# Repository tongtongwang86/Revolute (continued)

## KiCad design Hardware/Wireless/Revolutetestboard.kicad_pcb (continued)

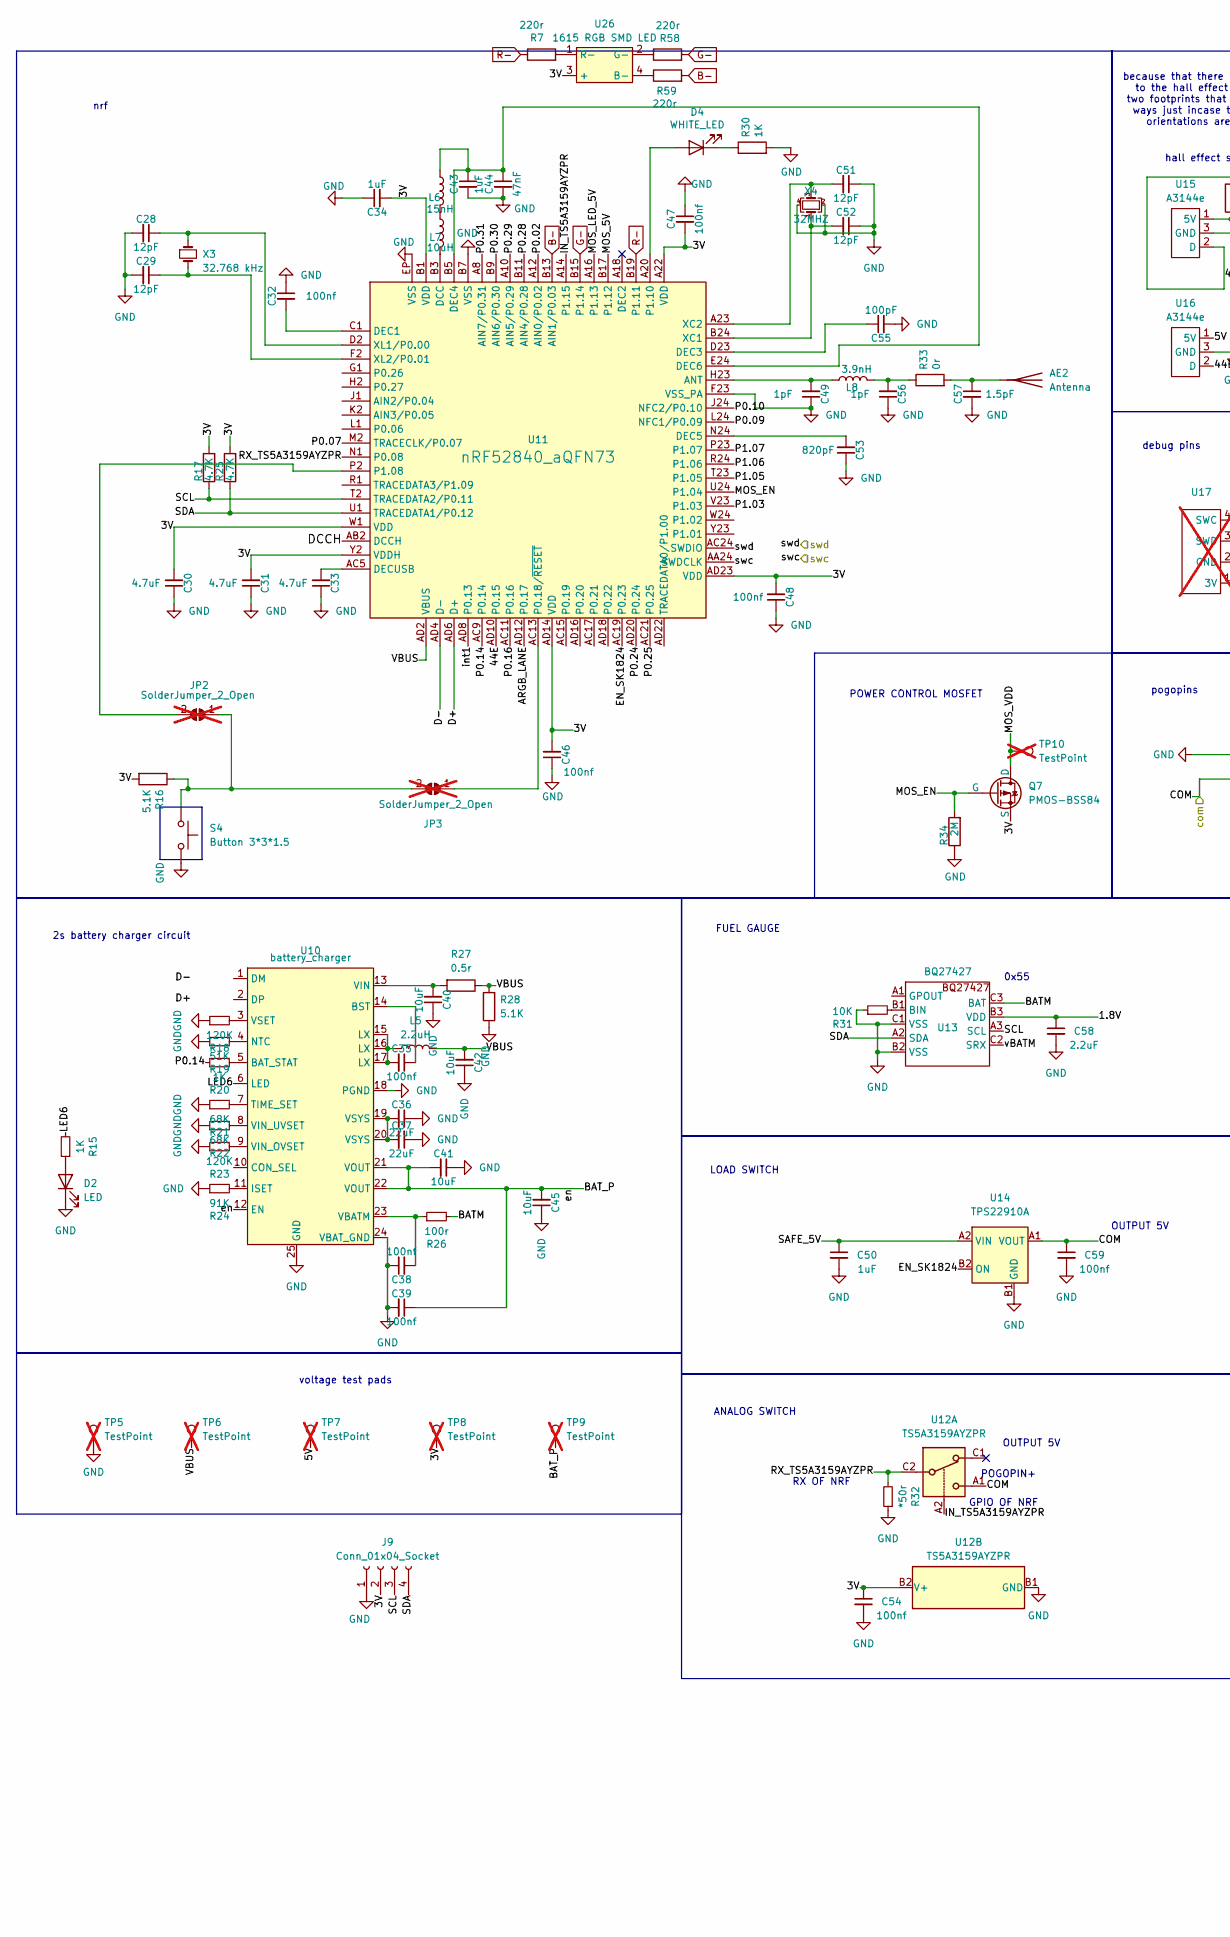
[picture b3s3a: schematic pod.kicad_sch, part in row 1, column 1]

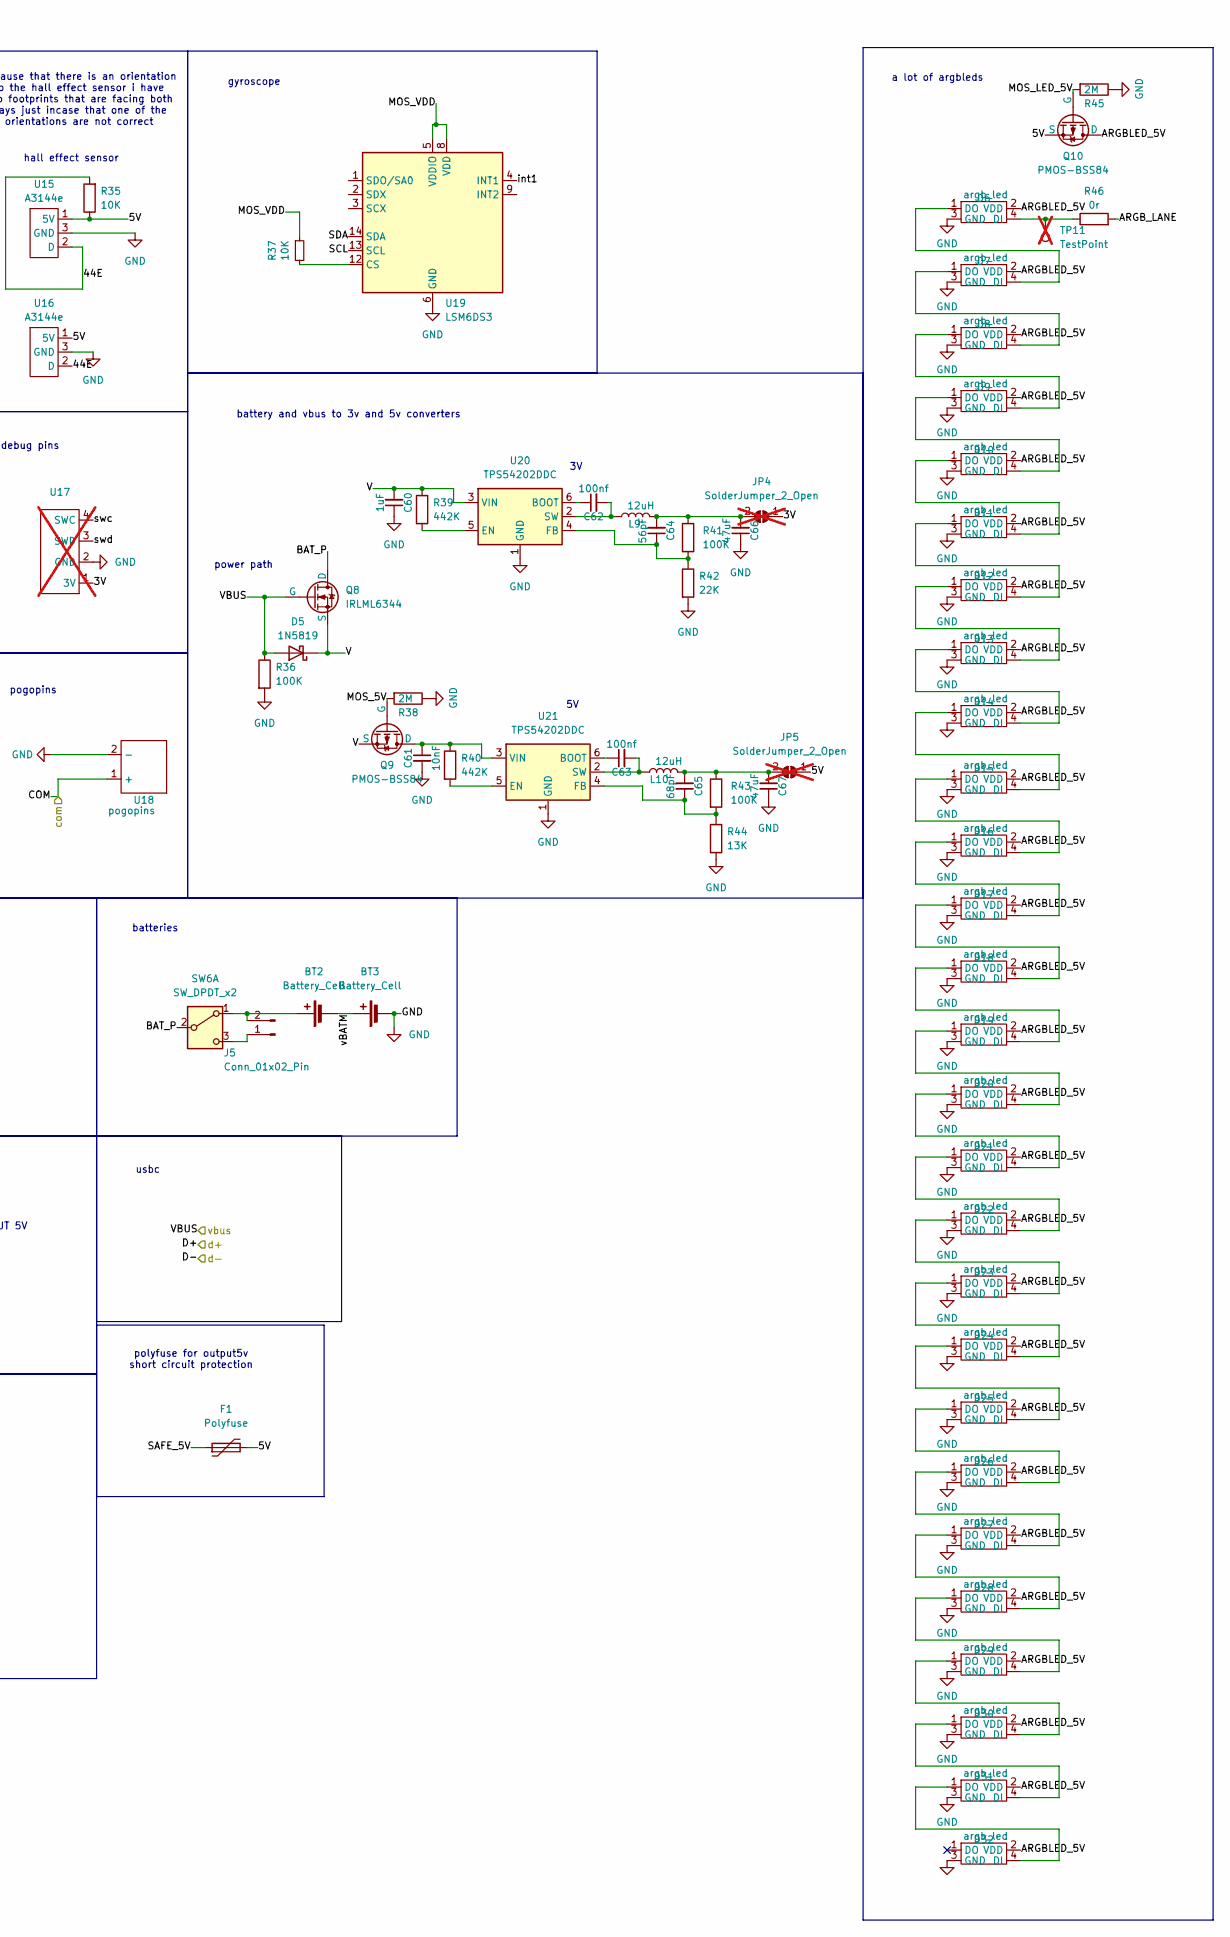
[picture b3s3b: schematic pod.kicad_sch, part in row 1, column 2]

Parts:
AE2: Antenna; 2.4GHz-meander-antenna
BT2, BT3: Battery_Cell; BatteryHolder_Keystone_1057_1x2032
C28, C29, C51, C52: 12pF; 0402
C30, C31, C33: 4.7uF; 0402
C32, C35, C38, C39, C46, C47, C48, C54, C59, C62, C63: 100nf; 0402
C34, C43, C50, C60: 1uF; 0402
C36, C37: 22uF; 0402
C40, C41, C42, C45: 10uF; 0402
C44: 47nF; 0402
C49, C56: 1pF; 0402
C53: 820pF; 0402
C55: 100pF; 0402
C57: 1.5pF; 0402
C58: 2.2uF; 0402
C61: 10nF; 0402
C64: 56pF; 0402
C65: 68pF; 0402
C66, C67: 47uF; 0402
D2: LED; LED_0402_1005Metric
D4: WHITE_LED; LED_0402_1005Metric
D5: 1N5819; D_SOD-323_HandSoldering
D6, D7, D8, D9, D10, D11, D12, D13, D14, D15, D16, D17, D18, D19, D20, D21, D22, D23, D24, D25, D26, D27, D28, D29, D30, D31, D32: argb_led; Led-ARGB
F1: Polyfuse; R_0805_2012Metric
J5: Conn_01x02_Pin; PinHeader_1x02_P2.54mm_Vertical
J9: Conn_01x04_Socket; PinSocket_1x04_P2.54mm_Vertical
JP2, JP3, JP4, JP5: SolderJumper_2_Open; SolderBridge; not fitted
L5: 2.2uH; L_Chilisin_BMRA00050520
L6: 15nH; 0402
L7: 10uH; 0402
L8: 3.9nH; L_0402_1005Metric
L9, L10: 12uH; L_0603_1608Metric
Q7, Q9, Q10: PMOS-BSS84; SOT-23-3
Q8: IRLML6344; TSOT-23
R7, R58, R59: 220r; R_0402_1005Metric
R15, R20, R30: 1K; R_0402_1005Metric
R16, R28: 5.1K; R_0402_1005Metric
R17, R25: 4.7K; 0402
R18, R23: 120K; R_0402_1005Metric
R19: 51K; R_0402_1005Metric
R21, R22: 68K; R_0402_1005Metric
R24: 91K; R_0402_1005Metric
R26: 100r; R_0402_1005Metric
R27: 0.5r; R_0402_1005Metric
R31: 10K; 0402
R32: *50r; R_0402_1005Metric
R33, R46: 0r; 0402
R34, R38, R45: 2M; 0402
R35, R37: 10K; R_0402_1005Metric
R36, R41, R43: 100K; R_0402_1005Metric
R39, R40: 442K; R_0402_1005Metric
R42: 22K; R_0402_1005Metric
R44: 13K; R_0402_1005Metric
S4: Button 3*3*1.5; button 3x3
SW6: SW_DPDT_x2; MST-12C05 SLIDEBUTTON
TP5, TP6, TP7, TP8, TP9, TP10, TP11: TestPoint; TestPoint_Pad_D1.0mm; not fitted
U10: battery_charger; QFN-24-1EP_4x4mm_P0.5mm_EP2.7x2.6mm
U11: nRF52840_aQFN73; AQFN-73-1EP_7x7mm_P0.5mm_NRF52840-custom
U12: TS5A3159AYZPR; Texas_DSBGA-6_0.9x1.4mm_Layout2x3_P0.5mm
U13: BQ27427; Texas_DSBGA-9_1.62mmx1.58mm_Layout3x3_P0.5mm
U14: TPS22910A; BGA4N50P2X2_88X88X50N
U15, U16: A3144e; TSOT-23
U17: debug pins; not fitted
U18: pogopins; pogopin
U19: LSM6DS3; LGA-14_3x2.5mm_P0.5mm_LayoutBorder3x4y
U20, U21: TPS54202DDC; SOT-23-6
U26: 1615 RGB SMD LED
X3: 32.768 kHz; Crystal_SMD_2012-2Pin_2.0x1.2mm; Manufacturer Part SC20S-12.5PF20PPM; LCSC Part C97607
X4: 32MHZ; Crystal_SMD_2016-4Pin_2.0x1.6mm

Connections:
/pod/1.8V: C58.1, U13.B3 (VDD)
/pod/3V: C30.2, C31.2, C34.2, C46.2, C47.2, C48.2, C54.1, J9.2, JP4.1 (A), Q7.2 (S), R16.2, R17.2, R25.2, TP8.1, U11.A22 (VDD), U11.AD14 (VDD), U11.AD23 (VDD), U11.B1 (VDD), U11.W1 (VDD), U11.Y2 (VDDH), U12.B2 (V+), U17.1 (3V), U26.3 (+)
/pod/5V: F1.2, JP5.1 (A), Q10.2 (S), R35.1, TP7.1, U15.1 (5V), U16.1 (5V)
/pod/44E: R35.2, U11.AD10 (P0.15), U15.2 (D), U16.2 (D)
/pod/ARGBLED_5V: D6.2 (VDD), D7.2 (VDD), D8.2 (VDD), D9.2 (VDD), D10.2 (VDD), D11.2 (VDD), D12.2 (VDD), D13.2 (VDD), D14.2 (VDD), D15.2 (VDD), D16.2 (VDD), D17.2 (VDD), D18.2 (VDD), D19.2 (VDD), D20.2 (VDD), D21.2 (VDD), D22.2 (VDD), D23.2 (VDD), D24.2 (VDD), D25.2 (VDD), D26.2 (VDD), D27.2 (VDD), D28.2 (VDD), D29.2 (VDD), D30.2 (VDD), D31.2 (VDD), D32.2 (VDD), Q10.3 (D)
/pod/ARGB_LANE: R46.2, U11.AD12 (P0.17)
/pod/BATM: R26.2, U13.C3 (BAT)
/pod/BAT_P: C39.1, C41.2, C45.2, Q8.3 (D), SW6.2 (B), TP9.1, U10.12 (EN), U10.21 (VOUT), U10.22 (VOUT)
/pod/COM: C59.1, U12.A1, U14.A1 (VOUT), U18.1 (+); also elsewhere on the board
/pod/D+: U11.AD6 (D+); also elsewhere on the board
/pod/D-: U11.AD4 (D-); also elsewhere on the board
/pod/DCCH: U11.AB2 (DCCH)
/pod/EN_SK1824: U11.AC19 (P0.23), U14.B2 (ON)
/pod/IN_TS5A3159AYZPR: U11.A14 (P1.15), U12.A2
/pod/LED6: R15.2, U10.6 (LED)
/pod/MOS_5V: Q9.1 (G), R38.2, U11.B17 (P1.12)
/pod/MOS_EN: Q7.1 (G), R34.2, U11.U24 (P1.04)
/pod/MOS_LED_5V: Q10.1 (G), R45.2, U11.A16 (P1.13)
/pod/MOS_VDD: Q7.3 (D), R37.1, TP10.1, U19.5 (VDDIO), U19.8 (VDD)
/pod/P0.02: U11.A12 (AIN0/P0.02)
/pod/P0.07: U11.M2 (TRACECLK/P0.07)
/pod/P0.09: U11.L24 (NFC1/P0.09)
/pod/P0.10: U11.J24 (NFC2/P0.10)
/pod/P0.14: R20.1, U11.AC9 (P0.14)
/pod/P0.16: U11.AC11 (P0.16)
/pod/P0.24: U11.AD20 (P0.24)
/pod/P0.25: U11.AC21 (P0.25)
/pod/P0.28: U11.B11 (AIN4/P0.28)
/pod/P0.29: U11.A10 (AIN5/P0.29)
/pod/P0.30: U11.B9 (AIN6/P0.30)
/pod/P0.31: U11.A8 (AIN7/P0.31)
/pod/P1.03: U11.V23 (P1.03)
/pod/P1.05: U11.T23 (P1.05)
/pod/P1.06: U11.R24 (P1.06)
/pod/P1.07: U11.P23 (P1.07)
/pod/RX_TS5A3159AYZPR: R32.2, U11.N1 (P0.08), U12.C2
/pod/SAFE_5V: C50.1, F1.1, U14.A2 (VIN)
/pod/SCL: J9.3, R17.1, U11.T2 (TRACEDATA2/P0.11), U13.A3 (SCL), U19.13 (SCL)
/pod/SDA: J9.4, R25.1, U11.U1 (TRACEDATA1/P0.12), U13.A2 (SDA), U19.14 (SDA)
/pod/V: C60.2, D5.1 (K), Q8.2 (S), Q9.2 (S), R39.1, U20.3 (VIN)
/pod/VBUS: C42.2, D5.2 (A), L5.2, Q8.1 (G), R27.1, R28.2, R36.1, TP6.1, U11.AD2 (VBUS); also elsewhere on the board
/pod/int1: U11.AD8 (P0.13), U19.4 (INT1)
/pod/swc: U11.AA24 (SWDCLK), U17.4 (SWC); also elsewhere on the board
/pod/swd: U11.AC24 (SWDIO), U17.3 (SWD); also elsewhere on the board
/pod/vBATM: BT2.2 (-), BT3.1 (+), U13.C2 (SRX)
B-: R59.2, U11.B13 (AIN1/P0.03)
G-: R58.2, U11.B15 (P1.14)
GND: BT3.2 (-), C28.2, C29.2, C30.1, C31.1, C32.1, C33.1, C34.1, C36.1, C37.1, C38.1, C39.2, C40.1, C41.1, C42.1, C43.2, C44.2, C45.1, C46.1, C47.1, C48.1, C49.1, C50.2, C51.1, C52.1, C53.1, C54.2, C55.2, C56.1, C57.2, C58.2, C59.2, C60.1, C61.2, C66.1, C67.1, D2.1 (K), D6.3 (GND), D7.3 (GND), D8.3 (GND), D9.3 (GND), D10.3 (GND), D11.3 (GND), D12.3 (GND), D13.3 (GND), D14.3 (GND), D15.3 (GND), D16.3 (GND), D17.3 (GND), D18.3 (GND), D19.3 (GND), D20.3 (GND), D21.3 (GND), D22.3 (GND), D23.3 (GND), D24.3 (GND), D25.3 (GND), D26.3 (GND), D27.3 (GND), D28.3 (GND), D29.3 (GND), D30.3 (GND), D31.3 (GND), D32.3 (GND), J9.1, R18.1, R19.1, R21.1, R22.1, R23.1, R24.1, R28.1, R30.2, R31.1, R32.1, R34.1, R36.2, R38.1, R42.2, R44.2, R45.1, S4.2, TP5.1, U10.18 (PGND), U10.24 (VBAT_GND), U10.25 (GND), U11.B7 (VSS), U11.EP (VSS), U11.F23 (VSS_PA), U12.B1 (GND), U13.B2 (VSS), U13.C1 (VSS), U14.B1 (GND), U15.3 (GND), U16.3 (GND), U17.2 (GND), U18.2 (-), U19.6 (GND), U19.7 (GND), U20.1 (GND), U21.1 (GND), X4.2, X4.4; also elsewhere on the board
unnamed: AE2.1 (A), C57.1, R33.2
unnamed: BT2.1 (+), J5.2, SW6.1 (A)
unnamed: C35.2, L5.1, U10.15 (LX), U10.16 (LX), U10.17 (LX)
unnamed: C36.2, C37.2, U10.19 (VSYS), U10.20 (VSYS)
unnamed: C56.2, L8.2, R33.1
unnamed: D2.2 (A), R15.1
unnamed: D4.2 (A), U11.A20 (P1.10)
unnamed: D4.1 (K), R30.1
unnamed: D6.4 (DI), R46.1, TP11.1
unnamed: D6.1 (DO), D7.4 (DI)
unnamed: D7.1 (DO), D8.4 (DI)
unnamed: D8.1 (DO), D9.4 (DI)
unnamed: D9.1 (DO), D10.4 (DI)
unnamed: D10.1 (DO), D11.4 (DI)
unnamed: D11.1 (DO), D12.4 (DI)
unnamed: D12.1 (DO), D13.4 (DI)
unnamed: D13.1 (DO), D14.4 (DI)
unnamed: D14.1 (DO), D15.4 (DI)
unnamed: D15.1 (DO), D16.4 (DI)
unnamed: D16.1 (DO), D17.4 (DI)
unnamed: D17.1 (DO), D18.4 (DI)
unnamed: D18.1 (DO), D19.4 (DI)
unnamed: D19.1 (DO), D20.4 (DI)
unnamed: D20.1 (DO), D21.4 (DI)
unnamed: D21.1 (DO), D22.4 (DI)
unnamed: D22.1 (DO), D23.4 (DI)
unnamed: D23.1 (DO), D24.4 (DI)
unnamed: D24.1 (DO), D25.4 (DI)
unnamed: D25.1 (DO), D26.4 (DI)
unnamed: D26.1 (DO), D27.4 (DI)
unnamed: D27.1 (DO), D28.4 (DI)
unnamed: D28.1 (DO), D29.4 (DI)
unnamed: D29.1 (DO), D30.4 (DI)
unnamed: D30.1 (DO), D31.4 (DI)
unnamed: D31.1 (DO), D32.4 (DI)
unnamed: J5.1, SW6.3 (C)
unnamed: JP2.1 (A), JP3.2 (B), R16.1, S4.1
unnamed: JP2.2 (B), U11.P2 (P1.08)
unnamed: JP3.1 (A), U11.AC13 (P0.18/~RESET)
unnamed: C64.2, C66.2, JP4.2 (B), L9.2, R41.1
unnamed: C65.2, C67.2, JP5.2 (B), L10.2, R43.1
unnamed: L6.2, L7.1
unnamed: C61.1, Q9.3 (D), R40.1, U21.3 (VIN)
unnamed: R20.2, U10.5 (BAT_STAT)
unnamed: C35.1, U10.14 (BST)
unnamed: R24.2, U10.11 (ISET)
unnamed: R19.2, U10.4 (NTC)
unnamed: R21.2, U10.7 (TIME_SET)
unnamed: C38.2, R26.1, U10.23 (VBATM)
unnamed: C40.2, R27.2, U10.13 (VIN)
unnamed: R23.2, U10.9 (VIN_OVSET)
unnamed: R22.2, U10.8 (VIN_UVSET)
unnamed: R18.2, U10.3 (VSET)
unnamed: C49.2, L8.1, U11.H23 (ANT)
unnamed: L7.2, U11.B3 (DCC)
unnamed: C32.2, U11.C1 (DEC1)
unnamed: C55.1, U11.D23 (DEC3)
unnamed: C43.1, C44.1, L6.1, U11.B5 (DEC4), U11.E24 (DEC6)
unnamed: C53.2, U11.N24 (DEC5)
unnamed: C33.2, U11.AC5 (DECUSB)
unnamed: C52.2, U11.B24 (XC1), X4.1
unnamed: C51.2, U11.A23 (XC2), X4.3
unnamed: C28.1, U11.D2 (XL1/P0.00), X3.1
unnamed: C29.1, U11.F2 (XL2/P0.01), X3.2
unnamed: R31.2, U13.B1 (BIN)
unnamed: R37.2, U19.12 (CS)
unnamed: C62.1, U20.6 (BOOT)
unnamed: R39.2, U20.5 (EN)
unnamed: C64.1, R41.2, R42.1, U20.4 (FB)
unnamed: C62.2, L9.1, U20.2 (SW)
unnamed: C63.1, U21.6 (BOOT)
unnamed: R40.2, U21.5 (EN)
unnamed: C65.1, R43.2, R44.1, U21.4 (FB)
unnamed: C63.2, L10.1, U21.2 (SW)
unnamed: R59.1, U26.4 (B-)
unnamed: R58.1, U26.2 (G-)
unnamed: R7.2, U26.1 (R-)
R-: R7.1, U11.B19 (P1.11)

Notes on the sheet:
a lot of argbleds
2s battery charger circuit
usbc
RX OF NRF
0x55
ANALOG SWITCH
POGOPIN+
polyfuse for output5v short circuit protection
OUTPUT 5V
power path
debug pins
battery and vbus to 3v and 5v converters
POWER CONTROL MOSFET
gyroscope
FUEL GAUGE
batteries
because that there is an orientation to the hall effect sensor i have two footprints that are facing both ways just incase that one of the orientations are not correct
voltage test pads
pogopins
nrf
hall effect sensor
LOAD SWITCH
GPIO OF NRF

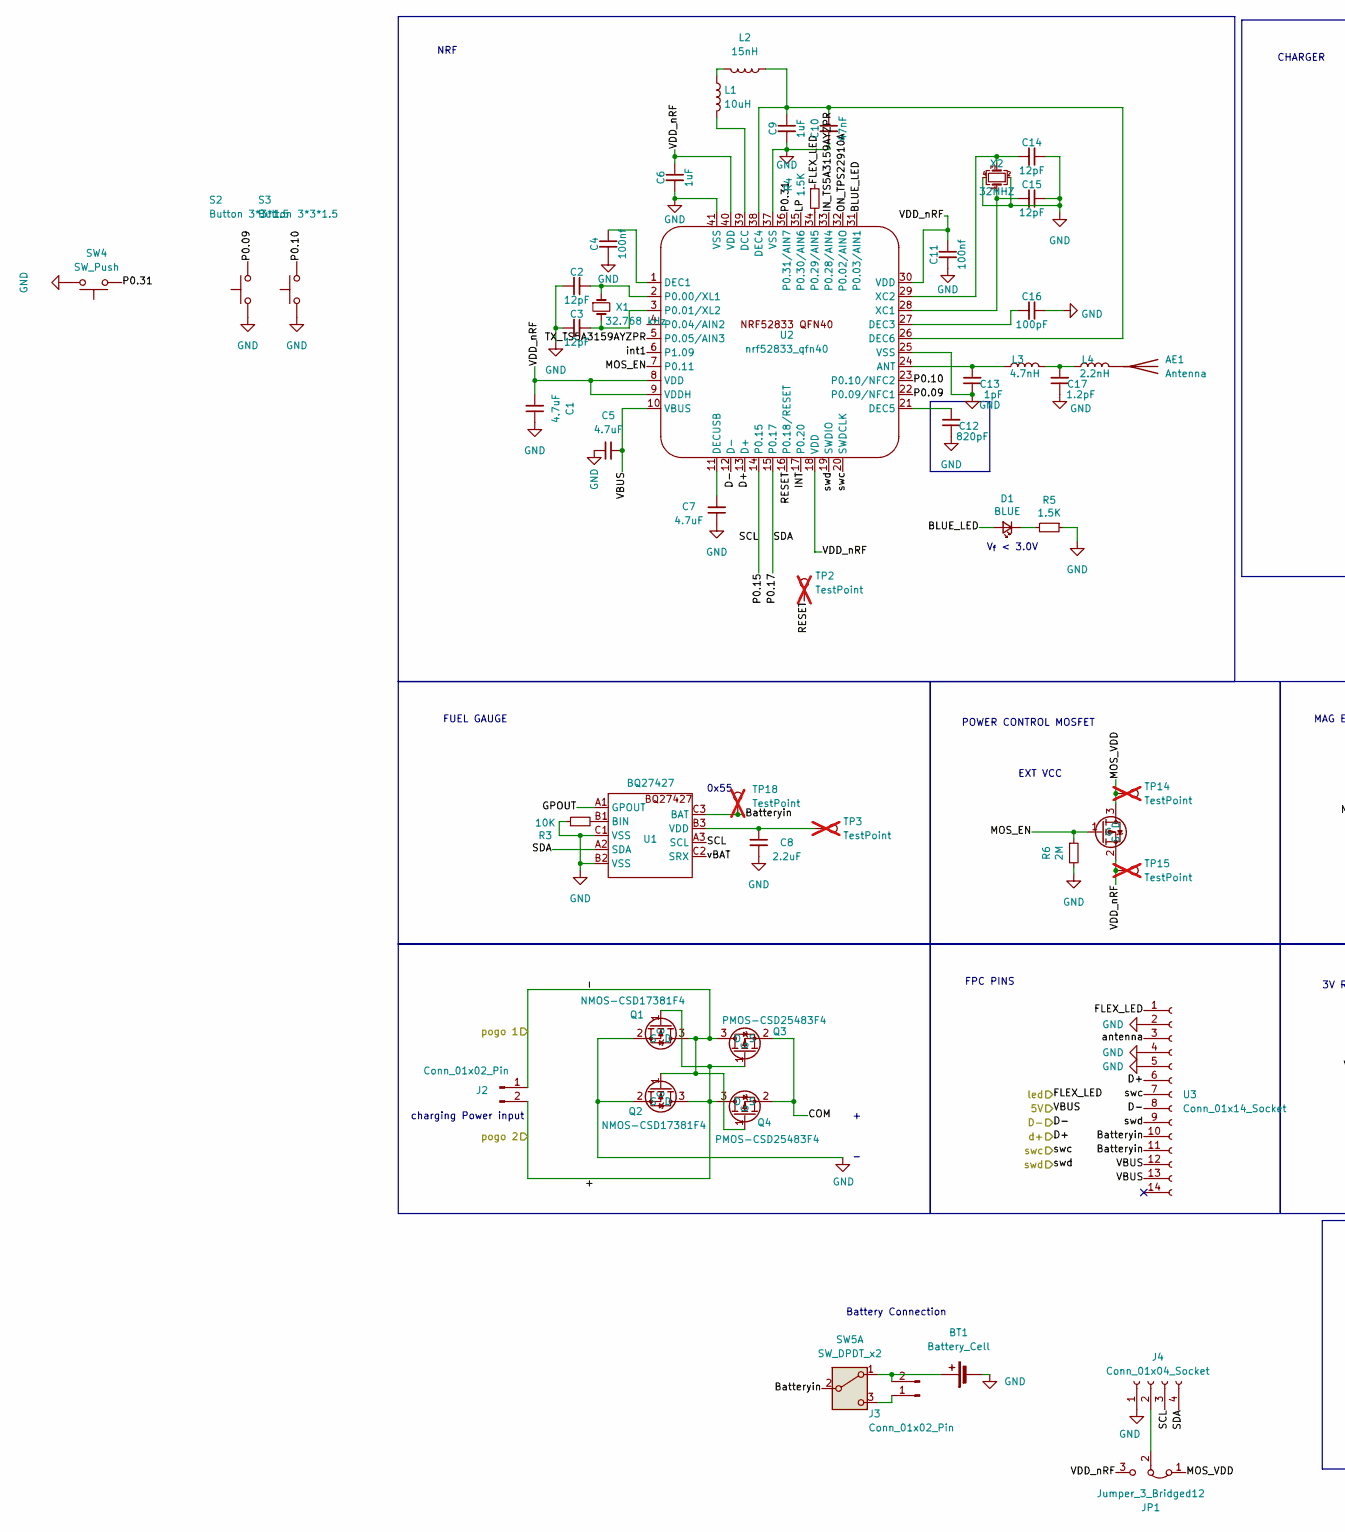
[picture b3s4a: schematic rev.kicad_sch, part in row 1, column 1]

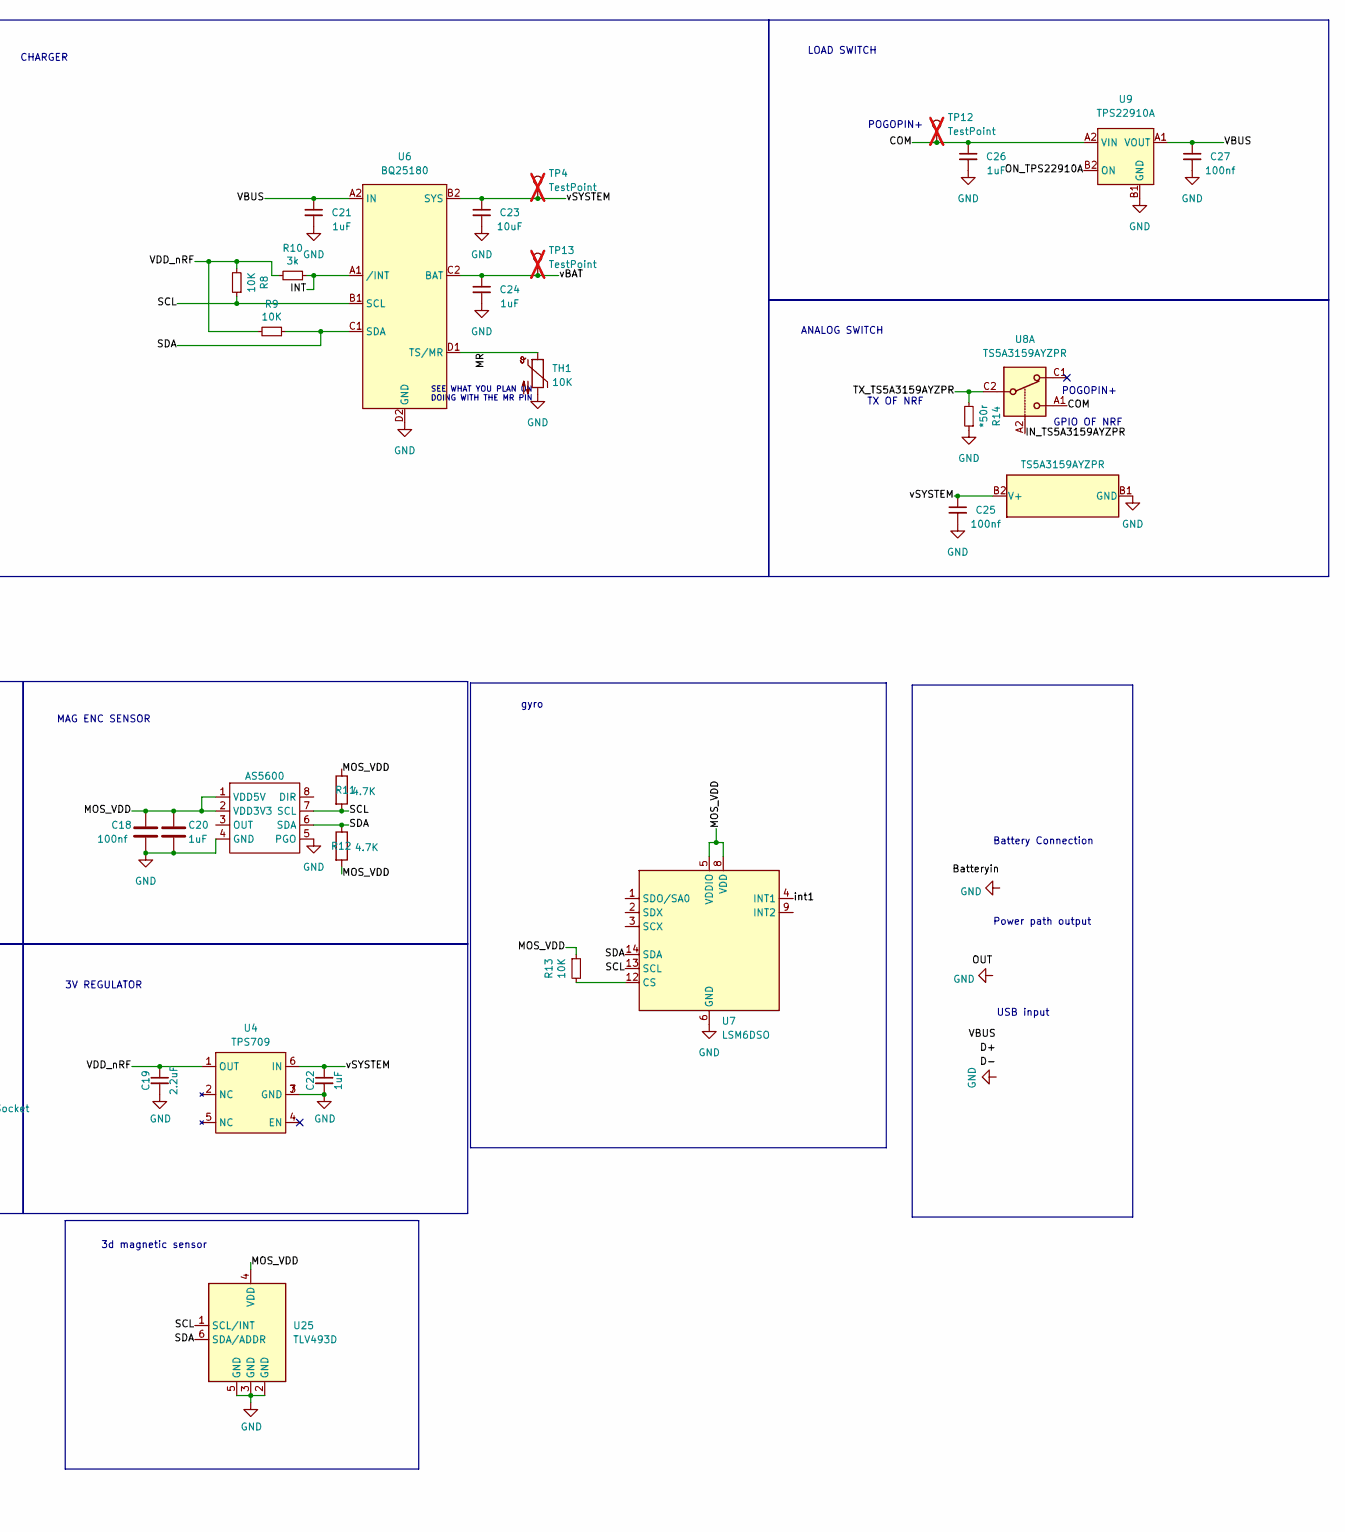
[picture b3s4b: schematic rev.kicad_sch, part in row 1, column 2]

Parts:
AE1: Antenna; 2.4GHz-meander-antenna
BT1: Battery_Cell; BatteryHolder_Keystone_1057_1x2032
C1, C5, C7: 4.7uF; 0402
C2, C3, C14, C15: 12pF; 0402
C4, C11, C18, C25, C27: 100nf; 0402
C6, C9, C20, C21, C22, C24, C26: 1uF; 0402
C8, C19: 2.2uF; 0402
C10: 47nF; 0402
C12: 820pF; 0402
C13: 1pF; 0402
C16: 100pF; 0402
C17: 1.2pF; 0402
C23: 10uF; 0402
D1: BLUE; LED_0402_1005Metric
J2, J3: Conn_01x02_Pin; PinHeader_1x02_P2.54mm_Vertical
J4: Conn_01x04_Socket; PinSocket_1x04_P2.54mm_Vertical
JP1: Jumper_3_Bridged12; SolderJumper-3_P1.3mm_Bridged12_RoundedPad1.0x1.5mm
L1: 10uH; 0402
L2: 15nH; 0402
L3: 4.7nH; 0402
L4: 2.2nH; 0402
Q1, Q2: NMOS-CSD17381F4; Mosfet0402
Q3, Q4, Q5: PMOS-CSD25483F4; Mosfet0402
R3, R13: 10K; 0402
R4, R5: 1.5K; 0402
R6: 2M; 0402
R8, R9: 10K; R_0402_1005Metric
R10: 3k; R_0402_1005Metric
R11, R12: 4.7K; 0402
R14: *50r; R_0402_1005Metric
S2, S3: Button 3*3*1.5; button 3x3
SW4: SW_Push; 16mmCompButton
SW5: SW_DPDT_x2; MST-12C05 SLIDEBUTTON
TH1: 10K; R_0402_1005Metric
TP2, TP3, TP4, TP12, TP13, TP14, TP15, TP18: TestPoint; TestPoint_Pad_D1.0mm; not fitted
U1: BQ27427; Texas_DSBGA-9_1.62mmx1.58mm_Layout3x3_P0.5mm
U2: nrf52833_qfn40; nrf52833
U3: Conn_01x14_Socket; FPC
U4: TPS709; DRV 6PIN
U5: AS5600; SOIC-8-1EP_3.9x4.9mm_P1.27mm_EP2.514x3.2mm
U6: BQ25180; Texas_DSBGA-8_0.705x1.468mm_Layout2x4_P0.4mm
U7: LSM6DSO; LGA-14_3x2.5mm_P0.5mm_LayoutBorder3x4y
U8: TS5A3159AYZPR; Texas_DSBGA-6_0.9x1.4mm_Layout2x3_P0.5mm
U9: TPS22910A; BGA4N50P2X2_88X88X50N
U25: TLV493D; SOT-23-6-Small
X1: 32.768 kHz; Crystal_SMD_2012-2Pin_2.0x1.2mm
X2: 32MHZ; Crystal_SMD_2016-4Pin_2.0x1.6mm

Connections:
/rev/+: J2.2, Q1.1 (G), Q2.3 (D), Q3.1 (G), Q4.3 (D); also elsewhere on the board
/rev/-: J2.1, Q1.3 (D), Q2.1 (G), Q3.3 (D), Q4.1 (G); also elsewhere on the board
/rev/BLUE_LED: D1.2 (A), U2.31 (P0.03/AIN1)
/rev/Batteryin: SW5.2 (B), TP18.1, U1.C3 (BAT), U3.10, U3.11
/rev/COM: C26.1, Q3.2 (S), Q4.2 (S), TP12.1, U8.A1, U9.A2 (VIN)
/rev/D+: U2.13 (D+), U3.6; also elsewhere on the board
/rev/D-: U2.12 (D-), U3.8; also elsewhere on the board
/rev/FLEX_LED: R4.1, U3.1; also elsewhere on the board
/rev/GPOUT: U1.A1 (GPOUT)
/rev/INT: R10.1, U2.17 (P0.20), U6.A1 (/INT)
/rev/IN_TS5A3159AYZPR: U2.33 (P0.28/AIN4), U8.A2
/rev/LP: U2.35 (P0.30/AIN6)
/rev/MOS_EN: Q5.1 (G), R6.1, U2.7 (P0.11)
/rev/MOS_VDD: C18.1, C20.1, JP1.1 (A), Q5.3 (D), R11.1, R12.2, R13.1, TP14.1, U5.1 (VDD5V), U5.2 (VDD3V3), U7.5 (VDDIO), U7.8 (VDD), U25.4 (VDD)
/rev/MR: TH1.1, U6.D1 (TS/MR)
/rev/ON_TPS22910A: U2.32 (P0.02/AINO), U9.B2 (ON)
/rev/P0.09: S2.2, U2.22 (P0.09/NFC1)
/rev/P0.10: S3.2, U2.23 (P0.10/NFC2)
/rev/P0.15: J4.3, R8.1, R11.2, U1.A3 (SCL), U2.14 (P0.15), U5.7 (SCL), U6.B1 (SCL), U7.13 (SCL), U25.1 (SCL/INT)
/rev/P0.17: J4.4, R9.1, R12.1, U1.A2 (SDA), U2.15 (P0.17), U5.6 (SDA), U6.C1 (SDA), U7.14 (SDA), U25.6 (SDA/ADDR)
/rev/P0.31: SW4.1, U2.36 (P0.31/AIN7)
/rev/RESET: TP2.1, U2.16 (P0.18/RESET)
/rev/TX_TS5A3159AYZPR: R14.2, U2.5 (P0.05/AIN3), U8.C2
/rev/VBUS: C5.1, C21.1, C27.1, U2.10 (VBUS), U3.12, U3.13, U6.A2 (IN), U9.A1 (VOUT); also elsewhere on the board
/rev/VDD_nRF: C1.2, C6.1, C11.1, C19.1, JP1.3 (B), Q5.2 (S), R8.2, R9.2, R10.2, TP15.1, U2.8 (VDD), U2.9 (VDDH), U2.18 (VDD), U2.30 (VDD), U2.40 (VDD), U4.1 (OUT)
/rev/antenna: U3.3
/rev/int1: U2.6 (P1.09), U7.4 (INT1)
/rev/swc: U2.20 (SWDCLK), U3.7; also elsewhere on the board
/rev/swd: U2.19 (SWDIO), U3.9; also elsewhere on the board
/rev/vBAT: C24.1, TP13.1, U1.C2 (SRX), U6.C2 (BAT)
/rev/vSYSTEM: C22.1, C23.1, C25.1, TP4.1, U4.6 (IN), U6.B2 (SYS), U8.B2 (V+)
GND: BT1.2 (-), C1.1, C2.2, C3.2, C4.2, C5.2, C6.2, C7.1, C8.2, C9.2, C10.2, C11.2, C12.1, C13.1, C14.1, C15.1, C16.1, C17.1, C18.2, C19.2, C20.2, C21.2, C22.2, C23.2, C24.2, C25.2, C26.2, C27.2, J4.1, Q1.2 (S), Q2.2 (S), R3.1, R5.1, R6.2, R14.1, S2.1, S3.1, SW4.2, TH1.2, U1.B2 (VSS), U1.C1 (VSS), U2.25 (VSS), U2.37 (VSS), U2.41 (VSS), U3.2, U3.4, U3.5, U4.3 (GND), U4.7 (GND), U5.4 (GND), U5.5 (PGO), U6.D2 (GND), U7.6 (GND), U7.7 (GND), U8.B1 (GND), U9.B1 (GND), U25.2 (GND), U25.3 (GND), U25.5 (GND), X2.2, X2.4; also elsewhere on the board
unnamed: AE1.1 (A), L4.2
unnamed: BT1.1 (+), J3.2, SW5.1 (A)
unnamed: C17.2, L3.2, L4.1
unnamed: D1.1 (K), R5.2
unnamed: J3.1, SW5.3 (C)
unnamed: J4.2, JP1.2 (C)
unnamed: L1.1, L2.2
unnamed: R3.2, U1.B1 (BIN)
unnamed: C8.1, TP3.1, U1.B3 (VDD)
unnamed: C13.2, L3.1, U2.24 (ANT)
unnamed: L1.2, U2.39 (DCC)
unnamed: C4.1, U2.1 (DEC1)
unnamed: C16.2, U2.27 (DEC3)
unnamed: C9.1, C10.1, L2.1, U2.26 (DEC6), U2.38 (DEC4)
unnamed: C12.2, U2.21 (DEC5)
unnamed: C7.2, U2.11 (DECUSB)
unnamed: C2.1, U2.2 (P0.00/XL1), X1.1
unnamed: C3.1, U2.3 (P0.01/XL2), X1.2
unnamed: R4.2, U2.34 (P0.29/AIN5)
unnamed: C15.2, U2.28 (XC1), X2.1
unnamed: C14.2, U2.29 (XC2), X2.3
unnamed: R13.2, U7.12 (CS)

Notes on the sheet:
FPC PINS
LOAD SWITCH
ANALOG SWITCH
USB input
NRF
3V REGULATOR
MAG ENC SENSOR
V_{f} < 3.0V
charging Power input
POWER CONTROL MOSFET
3d magnetic sensor
EXT VCC
Battery Connection
CHARGER
POGOPIN+
TX OF NRF
Power path output
FUEL GAUGE
gyro
GPIO OF NRF
SEE WHAT YOU PLAN ON DOING WITH THE MR PIN
0x55

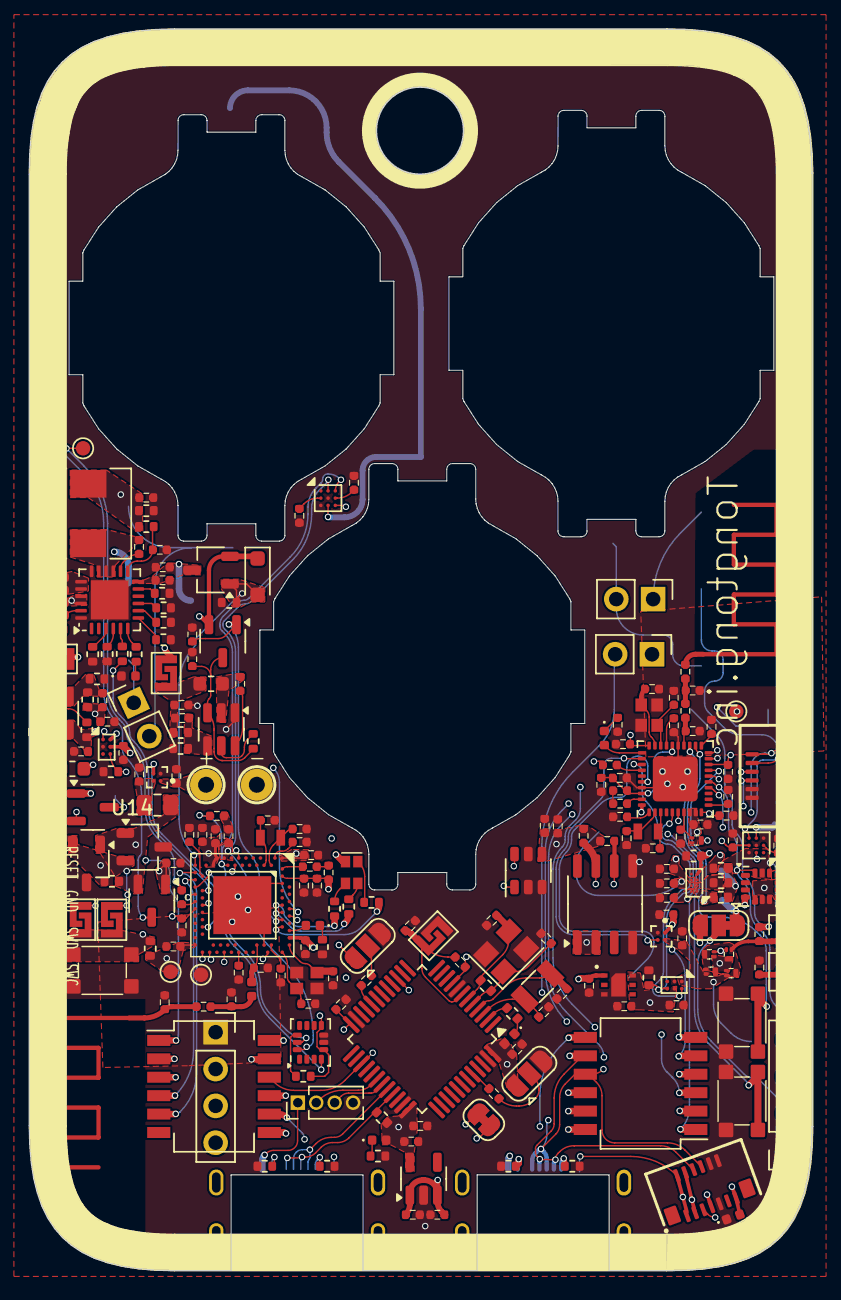
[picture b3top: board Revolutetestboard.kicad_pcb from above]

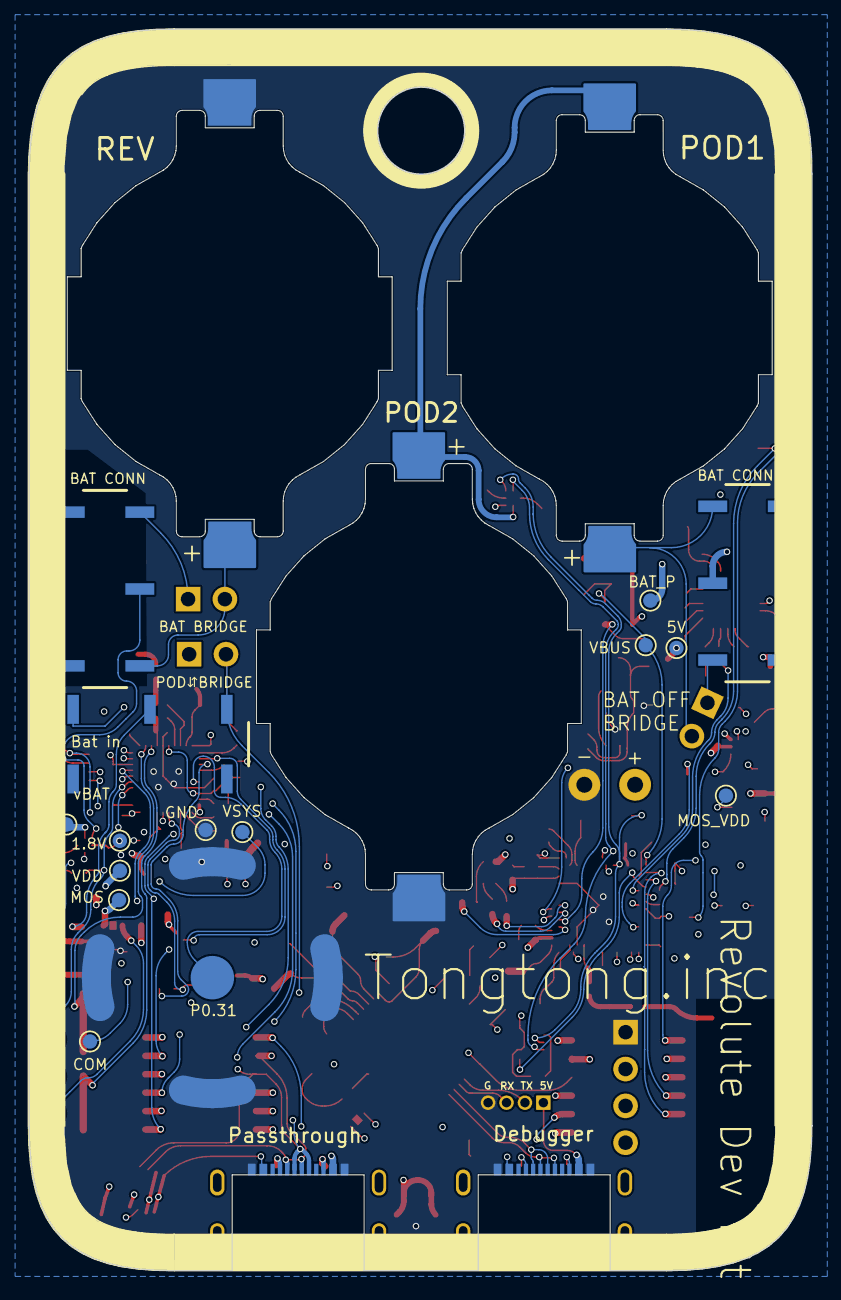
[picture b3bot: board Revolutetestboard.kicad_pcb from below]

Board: 4 copper layers, 54.0 x 85.6 mm, 271 parts (21 on the bottom side), 191 nets.

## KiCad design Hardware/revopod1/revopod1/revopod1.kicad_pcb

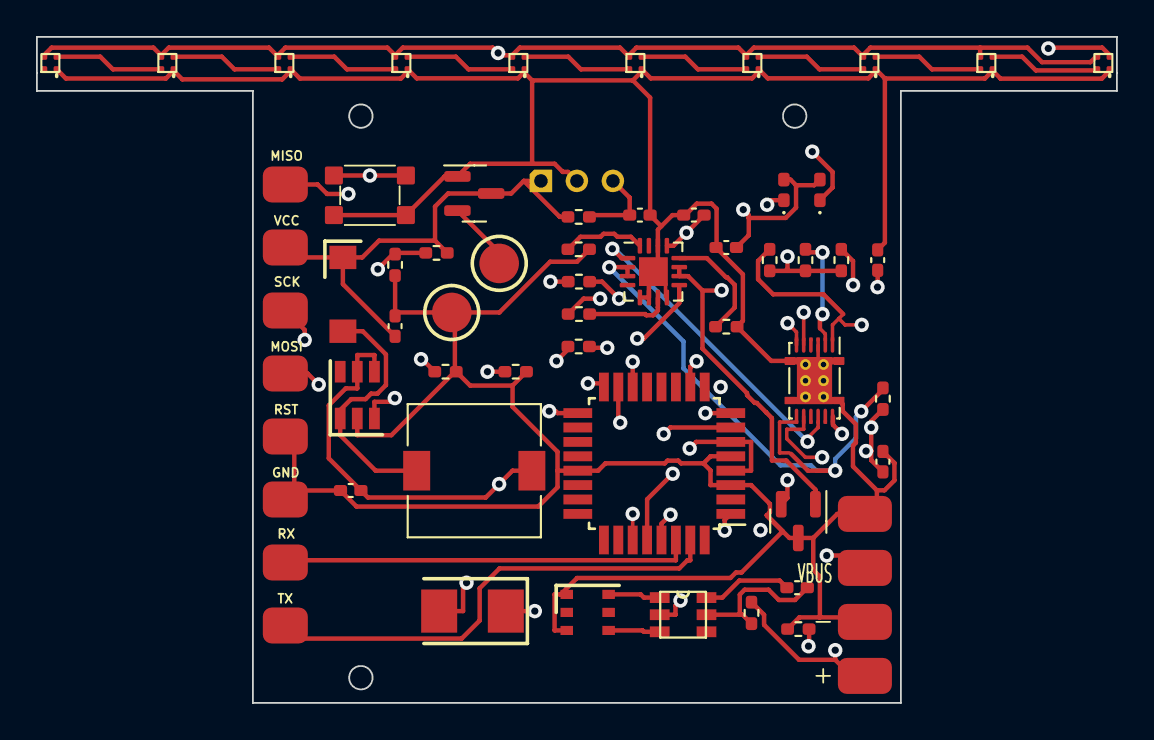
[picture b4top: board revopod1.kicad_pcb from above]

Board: 4 copper layers, 60.0 x 37.0 mm, 53 parts (0 on the bottom side), 45 nets.

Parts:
B1: 300mah; battery
C1, C3: 1uF; C_0402_1005Metric_Pad0.74x0.62mm_HandSolder
C2: 0.47uF; C_0402_1005Metric_Pad0.74x0.62mm_HandSolder
C4: 4.7uF; C_0402_1005Metric_Pad0.74x0.62mm_HandSolder
C5: 0.1u; C_0402_1005Metric_Pad0.74x0.62mm_HandSolder
C6, C7, C8: 22uF; C_0402_1005Metric_Pad0.74x0.62mm_HandSolder
D1: LEDR; LED_0402_1005Metric_Pad0.77x0.64mm_HandSolder
D2: LEDB; LED_0402_1005Metric_Pad0.77x0.64mm_HandSolder
D3: SS34; D_SMA_Handsoldering
D4, D5, D6, D7, D8, D9, D10, D11, D12, D13: Led-ARGB
L1: 22uH; L_7.3x7.3_H4.5
Q1: 8205A
Q2: BSS84; SOT-23
R3: 0.01; R_0402_1005Metric_Pad0.72x0.64mm_HandSolder
R4, R5: 4.7k; R_0402_1005Metric_Pad0.72x0.64mm_HandSolder
R6, R15, R19: 10k; R_0402_1005Metric_Pad0.72x0.64mm_HandSolder
R7, R8: 1.1k; R_0402_1005Metric_Pad0.72x0.64mm_HandSolder
R9, R10, R14: 1k; R_0402_1005Metric_Pad0.72x0.64mm_HandSolder
R11: 2k; R_0402_1005Metric_Pad0.72x0.64mm_HandSolder
R12: 100; R_0402_1005Metric_Pad0.72x0.64mm_HandSolder
R13: 7.5k; R_0402_1005Metric_Pad0.72x0.64mm_HandSolder
R17, R18: 22pF; R_0402_1005Metric_Pad0.72x0.64mm_HandSolder
SW1: SW_Push; button 3x3
U1: BQ24075RGT; VQFN-16-1EP_3x3mm_P0.5mm_EP1.6x1.6mm
U2: BQ27441-G1; Texas_S-PDSO-N12
U3: MT3608
U4: ATmega328-A; TQFP-32_7x7mm_P0.8mm
U5: pogopins; pogopin
U6: FS312F-G
U7: arduinnno pinnnns; arduino pins
U8: A3144; a3144
U9: usbcpads
U11: APE8865NR-19-HF-3; SOT-23
Y1: 16mhz; Crystal_SMD_5032-2Pin_5.0x3.2mm

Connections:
3V: C6.1, L1.2, R4.1, R5.1, R6.1, U3.4 (EN), U3.5 (IN), U11.2 (VO)
5V: C7.1, D3.1 (K), D4.2 (VDD), D5.2 (VDD), D6.2 (VDD), D7.2 (VDD), D8.2 (VDD), D9.2 (VDD), D10.2 (VDD), D11.2 (VDD), D12.2 (VDD), D13.2 (VDD), Q2.3 (D), R13.1, R19.1, U4.4 (VCC), U4.6 (VCC), U7.2 (VCC), U8.1 (5V)
B2: D4.4 (DI), U4.14 (PB2)
BAT+: B1.1 (+), C1.1, R3.1, R12.2, U2.6 (BAT), U2.8 (SRP)
BAT-: B1.2 (-), C1.2, C2.2, C3.2, C4.2, C6.2, C7.2, C8.1, D4.3 (GND), D5.3 (GND), D6.3 (GND), D7.3 (GND), D8.3 (GND), D9.3 (GND), D10.3 (GND), D11.3 (GND), D12.3 (GND), D13.3 (GND), Q1.1 (S1), Q1.3 (S2), Q2.1 (G), R7.1, R8.1, R11.2, R14.2, R17.1, R18.1, SW1.2, U1.5 (EN2), U1.6 (EN1), U1.8 (VSS), U1.14 (TMR), U1.17 (VSS), U2.3 (V_{SS}), U2.13 (PAD), U3.2 (GND), U4.3 (GND), U4.5 (GND), U4.21 (GND), U5.2 (-), U7.5 (RST), U7.6 (GND), U8.2 (GND), U9.2 (GND), U11.3 (GND)
FB: R13.2, R14.1, U3.3 (FB)
GPOUT: R6.2, U2.12 (GPOUT), U4.1 (PD3)
unnamed: D1.1 (K), R9.2
unnamed: D2.1 (K), R10.2
unnamed: D3.2 (A), L1.1, U3.1 (SW)
unnamed: D4.1 (DO), D5.4 (DI)
unnamed: D5.1 (DO), D6.4 (DI)
unnamed: D6.1 (DO), D7.4 (DI)
unnamed: D7.1 (DO), D8.4 (DI)
unnamed: D8.1 (DO), D9.4 (DI)
unnamed: D9.1 (DO), D10.4 (DI)
unnamed: D10.1 (DO), D11.4 (DI)
unnamed: D11.1 (DO), D12.4 (DI)
unnamed: D12.1 (DO), D13.4 (DI)
unnamed: Q2.2 (S), U5.1 (+)
unnamed: R7.2, U1.12 (ILIM)
unnamed: R8.2, U1.16 (ISET)
unnamed: R10.1, U1.9 (~CHG)
unnamed: C2.1, U2.5 (V_{DD})
unnamed: R15.1, SW1.1, U4.29 (~RESET/PC6)
unnamed: R11.1, U6.2 (CS)
unnamed: C5.1, U6.6 (GND)
unnamed: C5.2, R12.1, U6.5 (VCC)
OC: Q1.4 (G2), U6.3 (OC)
OD: Q1.6 (G1), U6.1 (OD)
OUT: C4.1, D1.2 (A), D2.2 (A), R15.2, U1.10 (OUT), U1.11 (OUT), U11.1 (VI)
PB3: U4.15 (PB3), U7.4 (MOSI)
PB4: U4.16 (PB4), U7.1 (MISO)
PB5: U4.17 (PB5), U7.3 (SCK)
PB6: R18.2, U4.7 (XTAL1/PB6), Y1.1
PB7: R17.2, U4.8 (XTAL2/PB7), Y1.2
PD6: C8.2, R19.2, U4.10 (PD6), U8.3 (D)
PGOOD: R9.1, U1.7 (~PGOOD)
RX: U4.30 (PD0), U7.7 (RX)
SCL: R5.2, U2.2 (SCL), U4.28 (PC5)
SDA: R4.2, U2.1 (SDA), U4.27 (PC4)
TS: U1.1 (TS), U2.10 (BIN)
TX: U4.31 (PD1), U7.8 (TX)
VBUS: C3.1, U1.13 (IN), U9.1 (VBUS)
V_BATT: R3.2, U1.2 (BAT), U1.3 (BAT), U2.7 (SRN)
